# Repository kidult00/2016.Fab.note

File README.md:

# 00's Fab Academy Notes

[Gitbook](https://www.gitbook.com/book/kidult00/00fabnotes)

## Week1

- [Introduction & Project Management](https://kidult00.gitbooks.io/00fabnotes/content/Week1/1_Introduction.html)
- [Assignment: Git & building a website](https://kidult00.gitbooks.io/00fabnotes/content/Week1/1_Assignment.html)

## Week2
- [Computer-aided Design](https://kidult00.gitbooks.io/00fabnotes/content/Week2/2_CAD.html)
- [Assignment: project modeling](https://kidult00.gitbooks.io/00fabnotes/content/Week2/2_Assignment.html)

## Week3
- [Computer-controlled cutting](https://kidult00.gitbooks.io/00fabnotes/content/Week3/3_computer-controlled%20cutting.html)
- [Assignment: A press-fit construction kit](https://kidult00.gitbooks.io/00fabnotes/content/Week3/3_Assignment.html)

## Week4
- [Electronics-production](https://kidult00.gitbooks.io/00fabnotes/content/Week4/4_electronics-production.html)
- [Assignment: PCB & FabISP](https://kidult00.gitbooks.io/00fabnotes/content/Week4/4_Assignment.html)

## Week5

- [3D scanning and printing](https://kidult00.gitbooks.io/00fabnotes/content/Week5/5_3D%20scanning%20and%20printing.html)
- [Assignment: 3D scanning and printing](https://kidult00.gitbooks.io/00fabnotes/content/Week5/5_Assignment.html)

## Week6

- [Electronics Design](https://kidult00.gitbooks.io/00fabnotes/content/Week6/6_ElectronicsDesign.html)
- [Assignment: Design and make a board](https://kidult00.gitbooks.io/00fabnotes/content/Week6/6_Assignment.html)

## Week7

- [Computer-controlled Machining](https://kidult00.gitbooks.io/00fabnotes/content/Week7/7_Computer-ControlledMachining.html)
- [Assignment: Design and make a board](https://kidult00.gitbooks.io/00fabnotes/content/Week7/7_Assignment.html)

## Week8

- [Embedded Programming](https://kidult00.gitbooks.io/00fabnotes/content/Week8/8_EmbeddedProgramming.html)
- [Assignment: Program the board](https://kidult00.gitbooks.io/00fabnotes/content/Week8/8_Assignment.html)

## Week9

- [Mechanical Design](https://kidult00.gitbooks.io/00fabnotes/content/Week9/9_MechanicalDesign.html)
- [Assignment: Make a machine](https://kidult00.gitbooks.io/00fabnotes/content/Week9/9_Assignment.html)

## Week10

- [Machine Design](https://kidult00.gitbooks.io/00fabnotes/content/Week10/10_MachineDesign.html)
- [Assignment: Make a machine](https://kidult00.gitbooks.io/00fabnotes/content/Week10/10_Assignment.html)

## Week11

- [Input Devices](https://kidult00.gitbooks.io/00fabnotes/content/Week11/11_InputDevices.html)
- [Assignment: Read a sensor](https://kidult00.gitbooks.io/00fabnotes/content/Week11/11_Assignment.html)

## Week12

- [Molding & Casting](https://kidult00.gitbooks.io/00fabnotes/content/Week12/12_MoldingandCasting.html)
- [Assignment: 3D Molding](https://kidult00.gitbooks.io/00fabnotes/content/Week12/12_Assignment.html)

## Week13

- [Output Devices](https://kidult00.gitbooks.io/00fabnotes/content/Week13/13_OutputDevices.html)
- [Assignment: Output Devices](https://kidult00.gitbooks.io/00fabnotes/content/Week13/13_Assignment.html)

## Week14

- [Composites](https://kidult00.gitbooks.io/00fabnotes/content/Week14/14_Composites.html)
- [Assignment: Composites](https://kidult00.gitbooks.io/00fabnotes/content/Week14/14_Assignment.html)

## Week15

- [Networking & Communications](https://kidult00.gitbooks.io/00fabnotes/content/Week15/15_Networking&Communications.html)
- [Assignment: Networking & Communications](https://kidult00.gitbooks.io/00fabnotes/content/Week15/15_Assignment.html)

## Week16

- [Interface & Application Programming](https://kidult00.gitbooks.io/00fabnotes/content/Week16/16_Interface&ApplicationProgramming.html)
- [Assignment: Interface & Application Programming](https://kidult00.gitbooks.io/00fabnotes/content/Week16/16_Assignment.html)

## Week17

- [Applications & Implications](https://kidult00.gitbooks.io/00fabnotes/content/Week17/17_Applications&Implications.html)
- [Assignment: Proposal for Final Project](https://kidult00.gitbooks.io/00fabnotes/content/Week17/17_Assignment.html)

## Week18

- [Invention, Intellectual Property and Income](https://kidult00.gitbooks.io/00fabnotes/content/Week18/18_Invention-IntellectualProperty-Income.html)
- [Assignment: Dissemination for Final Project](https://kidult00.gitbooks.io/00fabnotes/content/Week18/18_Assignment.html)

## Final Project

- [Mini SoundBot](https://kidult00.gitbooks.io/00fabnotes/content/FinalProject/project.html)

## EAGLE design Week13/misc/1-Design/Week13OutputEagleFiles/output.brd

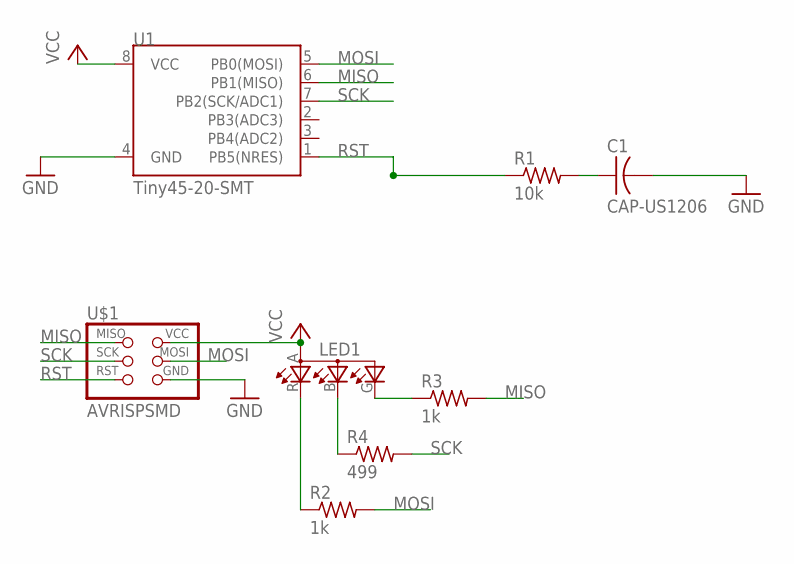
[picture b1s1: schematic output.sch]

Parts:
C1: CAP-US1206; C1206
LED1: LEDRGBOLD; P-LCC-4-3
R1: 10k; M1206
R2, R3: 1k; M1206
R4: 499; M1206
U1: Tiny45-20-SMT; SO08-EIAJ
U$1: AVRISPSMD; 2X03SMD

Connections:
GND: C1.2, U1.4 (GND), U$1.6 (GND)
MISO: R3.2, U1.6 (PB1(MISO)), U$1.1 (MISO)
MOSI: R2.2, U1.5 (PB0(MOSI)), U$1.4 (MOSI)
unnamed: C1.1, R1.2
unnamed: LED1.R (CRED), R2.1
unnamed: LED1.G (CGREEN), R3.1
unnamed: LED1.B (CBLUE), R4.1
RST: R1.1, U1.1 (PB5(NRES)), U$1.5 (RST)
SCK: R4.2, U1.7 (PB2(SCK/ADC1)), U$1.3 (SCK)
VCC: LED1.A (A2), U1.8 (VCC), U$1.2 (VCC)

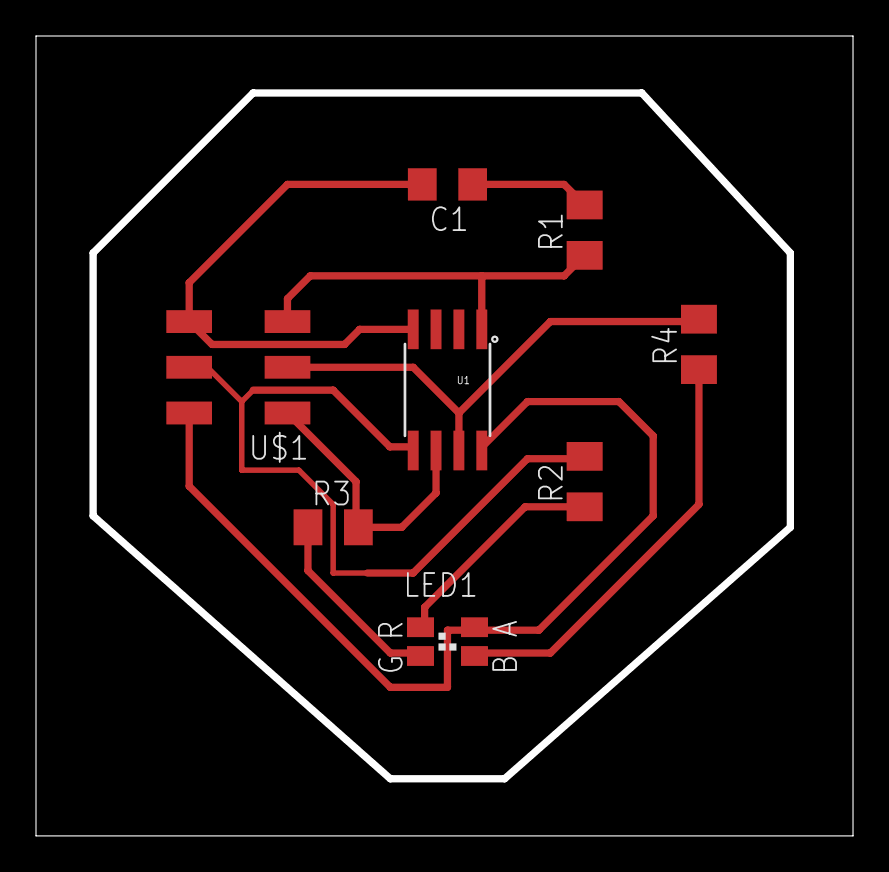
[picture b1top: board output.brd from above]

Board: 2 copper layers, 45.0 x 44.0 mm, 8 parts (0 on the bottom side), 10 nets.

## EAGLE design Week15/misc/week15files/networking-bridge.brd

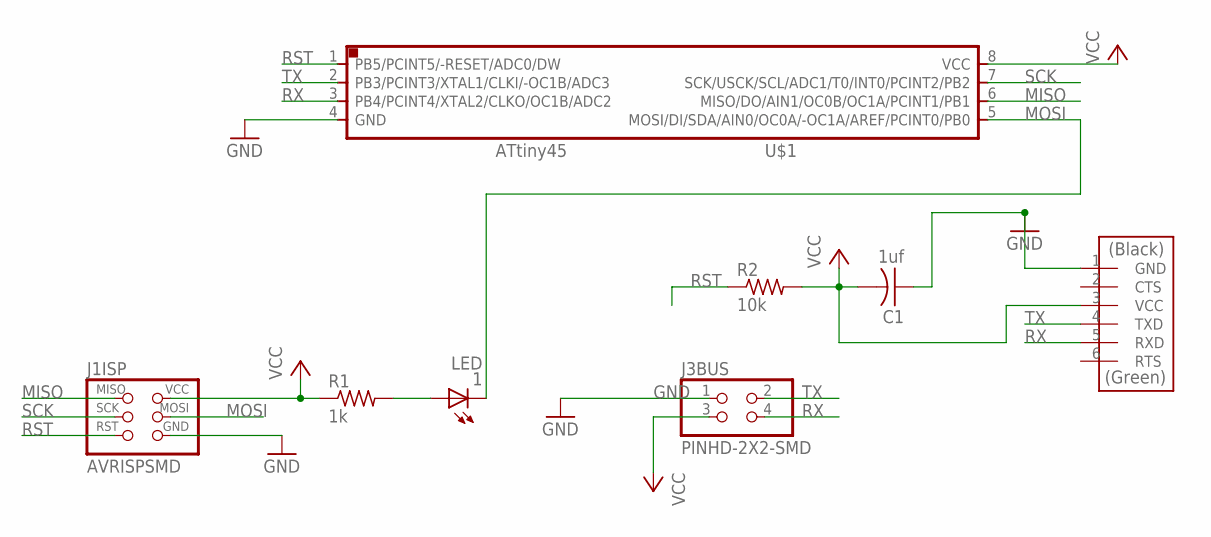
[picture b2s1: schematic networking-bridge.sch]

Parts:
1: LED; LED1206
C1: 1uf; C1206FAB
J1ISP: AVRISPSMD; 2X03SMD
J3BUS: PINHD-2X2-SMD; 2X02SMD
R1: 1k; R1206
R2: 10k; R1206
U$1: ATTINY45SI; SOIC8
U$2: FTDI-SMD-HEADER; 1X06SMD

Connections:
GND: C1.1, J1ISP.6 (GND), J3BUS.1, U$1.4 (GND), U$2.1 (GND)
MISO: J1ISP.1 (MISO), U$1.6 (MISO/DO/AIN1/OC0B/OC1A/PCINT1/PB1)
MOSI: 1.2 (C), J1ISP.4 (MOSI), U$1.5 (MOSI/DI/SDA/AIN0/OC0A/-OC1A/AREF/PCINT0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)
unnamed: 1.1 (A), R1.2
RST: J1ISP.5 (RST), R2.1, U$1.1 (PB5/PCINT5/-RESET/ADC0/DW)
RX: J3BUS.4, U$1.3 (PB4/PCINT4/XTAL2/CLKO/OC1B/ADC2), U$2.5 (RXD)
SCK: J1ISP.3 (SCK), U$1.7 (SCK/USCK/SCL/ADC1/T0/INT0/PCINT2/PB2)
TX: J3BUS.2, U$1.2 (PB3/PCINT3/XTAL1/CLKI/-OC1B/ADC3), U$2.4 (TXD)
VCC: C1.2, J1ISP.2 (VCC), J3BUS.3, R1.1, R2.2, U$1.8 (VCC), U$2.3 (VCC)

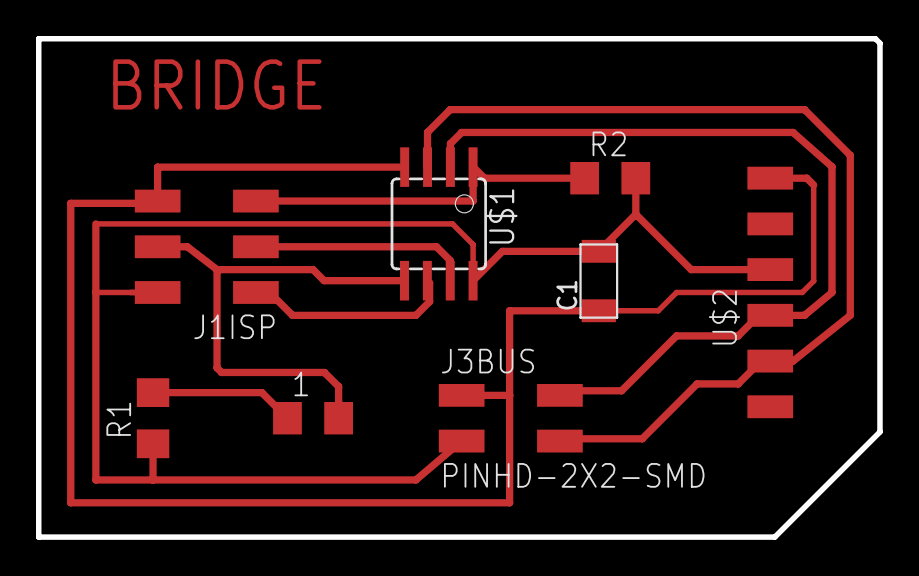
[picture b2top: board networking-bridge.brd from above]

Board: 2 copper layers, 46.7 x 27.7 mm, 8 parts (0 on the bottom side), 9 nets.

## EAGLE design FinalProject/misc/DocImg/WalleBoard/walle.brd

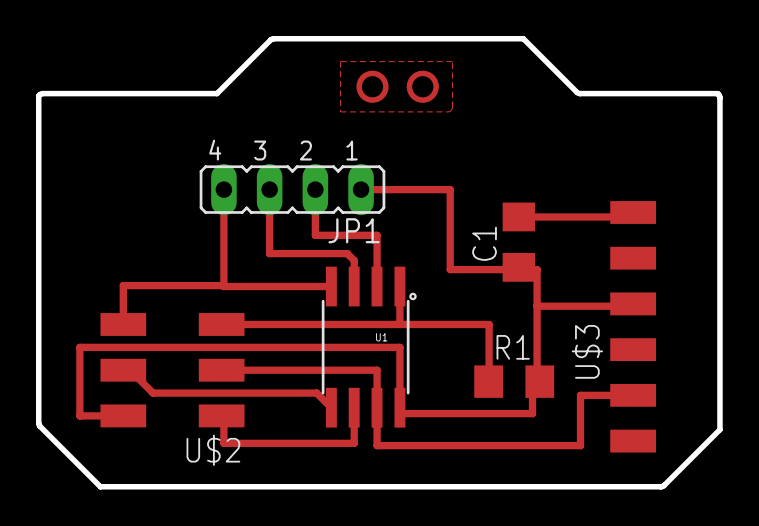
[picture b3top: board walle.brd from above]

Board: 2 copper layers, 37.8 x 24.9 mm, 6 parts (0 on the bottom side), 9 nets.

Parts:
C1: C1206
JP1: JP4
R1: R1206
U1: Tiny45-20-SMT; SO08-EIAJ
U$2: AVRISPSMD; 2X03SMD
U$3: FTDI-SMD-HEADER; 1X06SMD

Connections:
ECHO: JP1.3, U1.3
GND: JP1.4, U1.4, U$2.6
MISO: U1.6, U$2.1
MOSI: U1.5, U$2.4
unnamed: C1.1, JP1.1, R1.2, U1.8, U$2.2, U$3.3
unnamed: C1.2, U$3.1
PB5: R1.1, U1.1, U$2.5
SCK: U1.7, U$2.3, U$3.5
TRIG: JP1.2, U1.2

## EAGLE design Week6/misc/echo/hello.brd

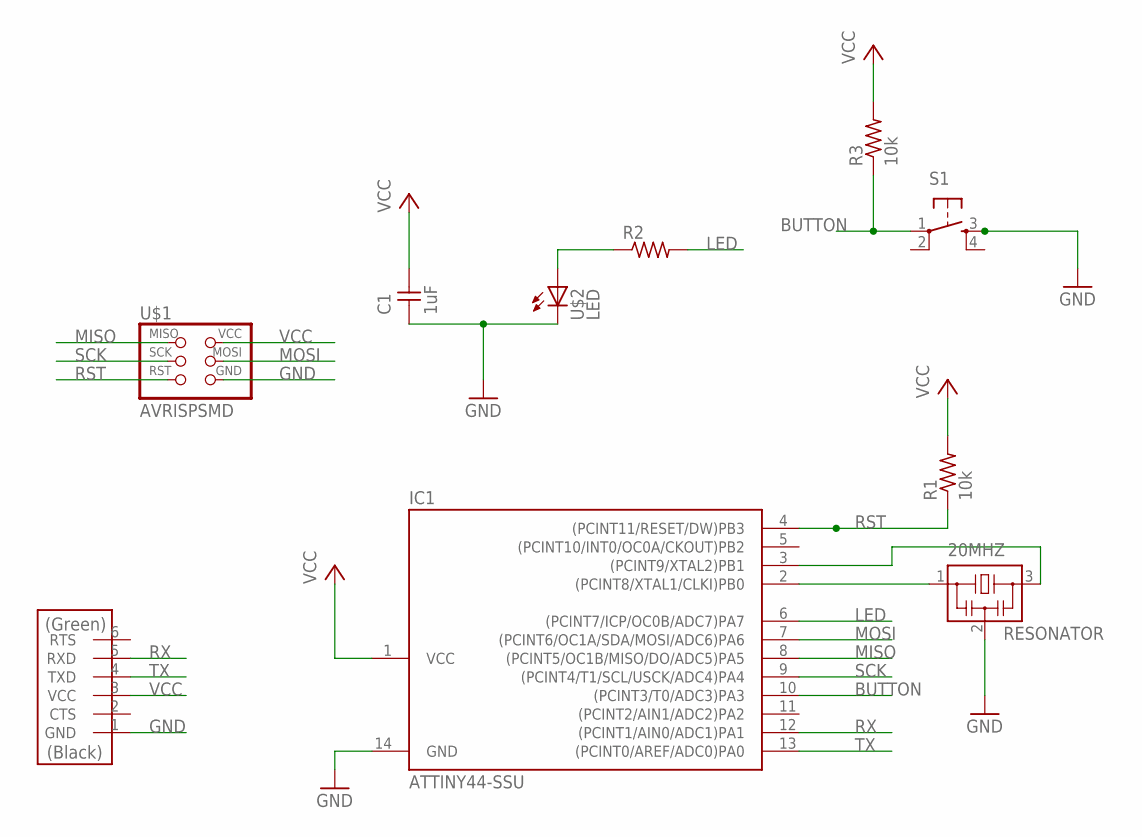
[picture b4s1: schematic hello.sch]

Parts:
20MHZ: RESONATOR; EFOBM
C1: 1uF; C1206
IC1: ATTINY44-SSU; SOIC14
R1, R3: 10k; R1206
R2: RES-US1206; R1206
S1: 6MM_SWITCH6MM_SWITCH; 6MM_SWITCH
U$1: AVRISPSMD; 2X03SMD
U$2: LED; LED1206
U$4: FTDI-SMD-HEADER; 1X06SMD

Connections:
BUTTON: IC1.10 ((PCINT3/T0/ADC3)PA3), R3.1, S1.1
GND: 20MHZ.2, C1.1, IC1.14 (GND), S1.3 (S), U$1.6 (GND), U$2.2 (C), U$4.1 (GND)
LED: IC1.6 ((PCINT7/ICP/OC0B/ADC7)PA7), R2.2
MISO: IC1.8 ((PCINT5/OC1B/MISO/DO/ADC5)PA5), U$1.1 (MISO)
MOSI: IC1.7 ((PCINT6/OC1A/SDA/MOSI/ADC6)PA6), U$1.4 (MOSI)
unnamed: R2.1, U$2.1 (A)
unnamed: 20MHZ.3, IC1.3 ((PCINT9/XTAL2)PB1)
unnamed: 20MHZ.1, IC1.2 ((PCINT8/XTAL1/CLKI)PB0)
RST: IC1.4 ((PCINT11/RESET/DW)PB3), R1.1, U$1.5 (RST)
RX: IC1.12 ((PCINT1/AIN0/ADC1)PA1), U$4.5 (RXD)
SCK: IC1.9 ((PCINT4/T1/SCL/USCK/ADC4)PA4), U$1.3 (SCK)
TX: IC1.13 ((PCINT0/AREF/ADC0)PA0), U$4.4 (TXD)
VCC: C1.2, IC1.1 (VCC), R1.2, R3.2, U$1.2 (VCC), U$4.3 (VCC)

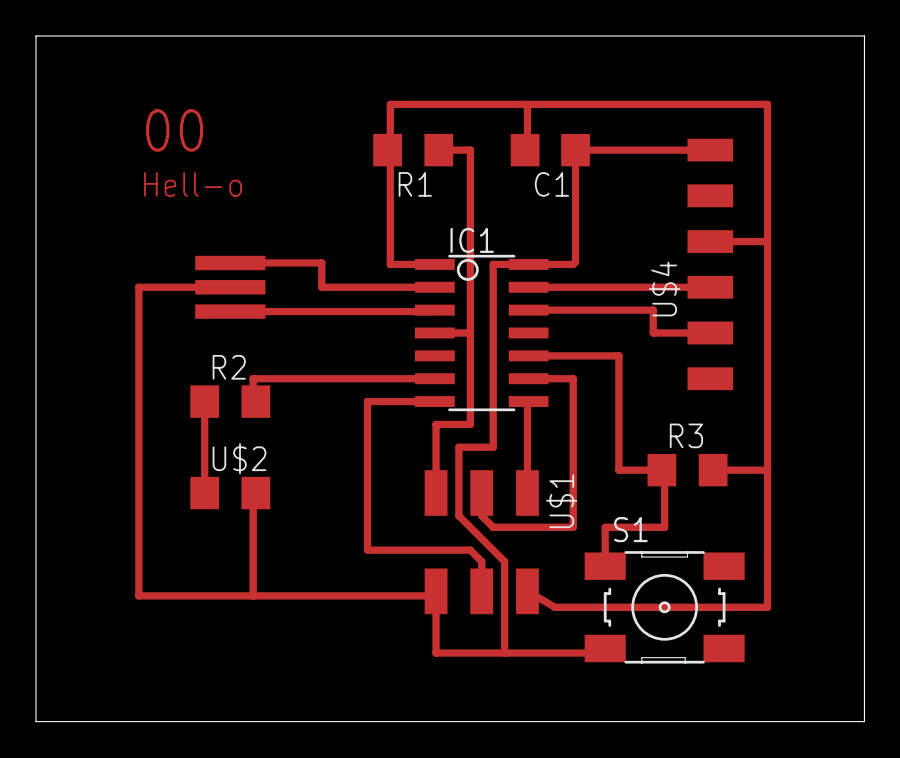
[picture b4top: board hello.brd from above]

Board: 2 copper layers, 46.0 x 38.1 mm, 10 parts (0 on the bottom side), 13 nets.

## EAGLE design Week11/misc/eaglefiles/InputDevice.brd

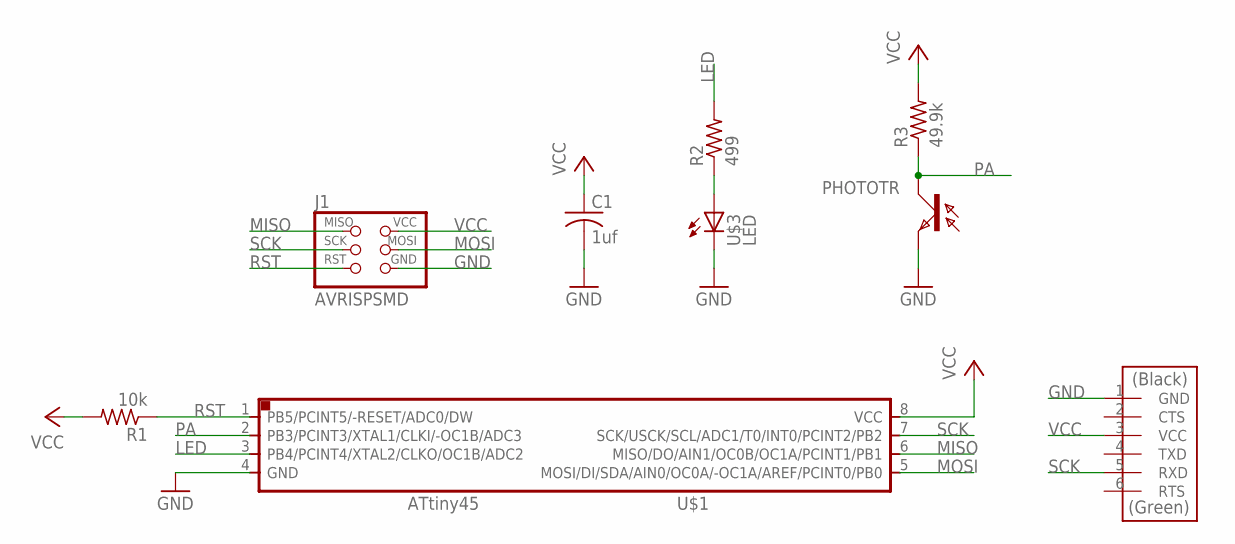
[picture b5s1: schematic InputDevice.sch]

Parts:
C1: 1uf; C1206
J1: AVRISPSMD; 2X03SMD
PHOTOTR: PHOTOTRANSISTOR-NPN1206; OP1206
R1: 10k; R1206
R2: 499; 1206
R3: 49.9k; 1206
U$1: ATTINY45SI; SOIC8
U$3: LED; 1206
U$4: FTDI-SMD-HEADER; 1X06SMD

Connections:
GND: C1.2, J1.6 (GND), PHOTOTR.EMITTER (E), U$1.4 (GND), U$3.2 (C), U$4.1 (GND)
LED: R2.2, U$1.3 (PB4/PCINT4/XTAL2/CLKO/OC1B/ADC2)
MISO: J1.1 (MISO), U$1.6 (MISO/DO/AIN1/OC0B/OC1A/PCINT1/PB1)
MOSI: J1.4 (MOSI), U$1.5 (MOSI/DI/SDA/AIN0/OC0A/-OC1A/AREF/PCINT0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)
unnamed: R2.1, U$3.1 (A)
PA: PHOTOTR.COLLECTOR (C), R3.1, U$1.2 (PB3/PCINT3/XTAL1/CLKI/-OC1B/ADC3)
RST: J1.5 (RST), R1.1, U$1.1 (PB5/PCINT5/-RESET/ADC0/DW)
SCK: J1.3 (SCK), U$1.7 (SCK/USCK/SCL/ADC1/T0/INT0/PCINT2/PB2), U$4.5 (RXD)
VCC: C1.1, J1.2 (VCC), R1.2, R3.2, U$1.8 (VCC), U$4.3 (VCC)

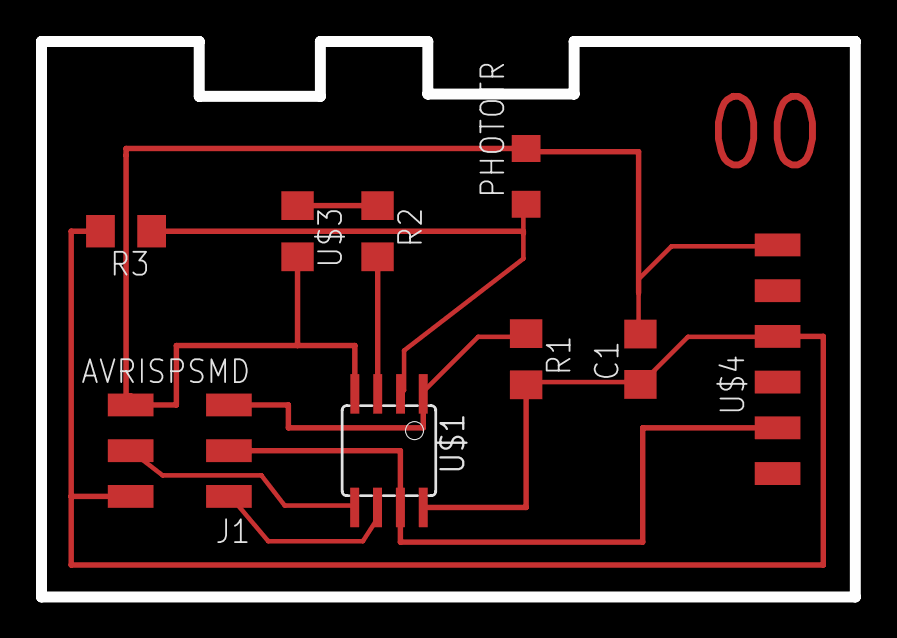
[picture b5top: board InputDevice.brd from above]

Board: 2 copper layers, 45.2 x 30.9 mm, 9 parts (0 on the bottom side), 9 nets.

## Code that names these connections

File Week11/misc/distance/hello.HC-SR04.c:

//
// hello.HC-SR04.c
//
// HC-SR04 sonar hello-world
//    9600 baud FTDI interface
//
// Neil Gershenfeld 11/15/15
// (c) Massachusetts Institute of Technology 2015
//
// This work may be reproduced, modified, distributed,
// performed, and displayed for any purpose. Copyright is
// retained and must be preserved. The work is provided
// as is; no warranty is provided, and users accept all 
// liability.
//

#include <avr/io.h>
#include <util/delay.h>

#define output(directions,pin) (directions |= pin) // set port direction for output
#define set(port,pin) (port |= pin) // set port pin
#define clear(port,pin) (port &= (~pin)) // clear port pin
#define pin_test(pins,pin) (pins & pin) // test for port pin
#define bit_test(byte,bit) (byte & (1 << bit)) // test for bit set
#define bit_delay_time 102 // bit delay for 9600 with overhead
#define bit_delay() _delay_us(bit_delay_time) // RS232 bit delay
#define half_bit_delay() _delay_us(bit_delay_time/2) // RS232 half bit delay
#define char_delay() _delay_ms(10) // char delay

#define serial_port PORTB
#define serial_direction DDRB
#define serial_pin_out (1 << PB2)
#define trigger_port PORTB
#define trigger_direction DDRB
#define trigger_pin (1 << PB3)
#define echo_pins PINB
#define echo_direction DDRB
#define echo_pin (1 << PB4)

#define timeout 255

void put_char(volatile unsigned char *port, unsigned char pin, char txchar) {
   //
   // send character in txchar on port pin
   //    assumes line driver (inverts bits)
   //
   // start bit
   //
   clear(*port,pin);
   bit_delay();
   //
   // unrolled loop to write data bits
   //
   if bit_test(txchar,0)
      set(*port,pin);
   else
      clear(*port,pin);
   bit_delay();
   if bit_test(txchar,1)
      set(*port,pin);
   else
      clear(*port,pin);
   bit_delay();
   if bit_test(txchar,2)
      set(*port,pin);
   else
      clear(*port,pin);
   bit_delay();
   if bit_test(txchar,3)
      set(*port,pin);
   else
      clear(*port,pin);
   bit_delay();
   if bit_test(txchar,4)
      set(*port,pin);
   else
      clear(*port,pin);
   bit_delay();
   if bit_test(txchar,5)
      set(*port,pin);
   else
      clear(*port,pin);
   bit_delay();
   if bit_test(txchar,6)
      set(*port,pin);
   else
      clear(*port,pin);
   bit_delay();
   if bit_test(txchar,7)
      set(*port,pin);
   else
      clear(*port,pin);
   bit_delay();
   //
   // stop bit
   //
   set(*port,pin);
   bit_delay();
   //
   // char delay
   //
   bit_delay();
   }

int main(void) {
   //
   // main
   //
   static unsigned char high,low;
   //
   // set clock divider to /1
   //
   CLKPR = (1 << CLKPCE);
   CLKPR = (0 << CLKPS3) | (0 << CLKPS2) | (0 << CLKPS1) | (0 << CLKPS0);
   //
   // initialize output pins
   //
   set(serial_port,serial_pin_out);
   output(serial_direction,serial_pin_out);
   clear(trigger_port,trigger_pin);
   output(trigger_direction,trigger_pin);
   //
   // start counter
   //
   TCCR0B |= (1 << CS00); // prescale /1
   //
   // main loop
   //
   while (1) {
      //
      // trigger pulse
      //
      set(trigger_port,trigger_pin);
      _delay_us(10);
      clear(trigger_port,trigger_pin);  
      //
      // wait for echo rising edge
      //
      high = 0;
      TCNT0 = 0;
      TIFR |= (1 << TOV0);
      while (1) {
         if ((echo_pins & echo_pin) != 0) // check for rising edge
            break;
         if ((TIFR & (1 << TOV0)) != 0) { // check for counter overflow
            high += 1;
            if (high == timeout)
               break;
            TIFR |= (1 << TOV0);
            }
         }
      //
      // rising edge found, wait for falling edge
      //
      high = 0;
      TCNT0 = 0;
      TIFR |= (1 << TOV0);
      while (1) {
         if ((echo_pins & echo_pin) == 0) { // check for falling edge
            low = TCNT0;
            break;
            }
         if ((TIFR & (1 << TOV0)) != 0) { // check for counter overflow
            high += 1;
            if (high == timeout)
               break;
            TIFR |= (1 << TOV0);
            }
         }
      //
      // send count with framing
      //
      put_char(&serial_port,serial_pin_out,1);
      put_char(&serial_port,serial_pin_out,2);
      put_char(&serial_port,serial_pin_out,3);
      put_char(&serial_port,serial_pin_out,4);
      put_char(&serial_port,serial_pin_out,low);
      put_char(&serial_port,serial_pin_out,high);
      //
      // delay before next cycle
      //
      _delay_ms(10);
      }
   }

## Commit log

2016-01-24 creat notes
2016-01-28 first
2016-02-01 week1 notes
2016-02-01 disqus
2016-02-01 week1 assignment
2016-02-09 week2 assigment
2016-02-15 week3 update
2016-02-19 fabnotes002
2016-02-19 week4 update
2016-02-23 week3 assignment
2016-02-25 week5 note
2016-02-29 stl update
2016-02-29 week4 assignment update
2016-02-29 0229update
2016-03-01 0301update
2016-03-03 week6 update
2016-03-03 week5 pic
2016-03-05 update index
2016-03-09 update week5 assignment
2016-03-11 week7
2016-03-12 add week7
2016-03-12 cleanup
2016-03-17 add week8
2016-03-17 week8 note
2016-03-17 week6
2016-03-24 week8
2016-04-02 week9
2016-04-07 week10
2016-04-09 week8 update
2016-04-09 add week10
2016-04-14 week11
2016-04-21 week12
2016-04-23 week7 pics & week11 source
2016-04-28 week13 note
2016-04-29 week13
2016-05-01 new boards
2016-05-02 week12 update
2016-05-14 week14-15 note
2016-05-21 week15 update
2016-05-22 week11 update
2016-05-28 week16 update
2016-05-29 week11-13 update
2016-05-31 week11-12 update
2016-06-04 week11,13 update
2016-06-04 add week15,16
2016-06-09 add theremin scheme
2016-06-09 theremin
2016-06-10 week11/15 update
2016-06-11 final update
2016-06-12 final
2016-06-12 update week17
2016-06-14 rename
2016-06-21 coding update
2016-06-23 week18
2016-06-23 remove Mysonar
2016-06-27 week7/9/14 cutfile
2016-06-27 week1 update
2016-06-28 week2 update
2016-06-30 update 2-9
2016-06-30 update week10
2016-06-30 update week 10/18
2016-07-01 update week 10
2016-07-02 update final & week18
2016-07-03 update week 3/7
2016-07-06 update 7
2016-07-06 update week14
2016-07-06 update week15/18
2016-07-07 update week12 stl
2016-07-07 update week12
2016-07-22 finalproject
2016-07-22 week11/13/15/final
2016-07-24 refinements

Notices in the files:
parts and their libraries:
SparkFun-DigitalIC: Licensing: Creative Commons ShareAlike 4.0 International - https://creativecommons.org/licenses/by-sa/4.0
